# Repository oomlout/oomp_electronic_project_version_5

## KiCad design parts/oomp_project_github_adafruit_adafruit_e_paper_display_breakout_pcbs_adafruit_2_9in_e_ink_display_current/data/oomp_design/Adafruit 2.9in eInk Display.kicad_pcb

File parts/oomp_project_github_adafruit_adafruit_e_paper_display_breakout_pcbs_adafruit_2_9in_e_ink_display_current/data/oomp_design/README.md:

# OOMP KiCad design copy

Open `Adafruit 2.9in eInk Display.kicad_pro` (or the `.kicad_pcb` / `.kicad_sch`) in KiCad. Local OOMP libraries are under `libraries/`. Original inputs are preserved in [../original/](../original/).

Only verified unchanged installed KiCad defaults were renamed. Modified, custom, unmatched and unavailable items remain unchanged. Soldering variants are never swapped during conversion. Existing pad coordinates, nets and UUIDs are preserved.

See [conversion_report.yaml](conversion_report.yaml) for every conversion and skip. Copy this directory before editing; regeneration refuses to overwrite edited design files.

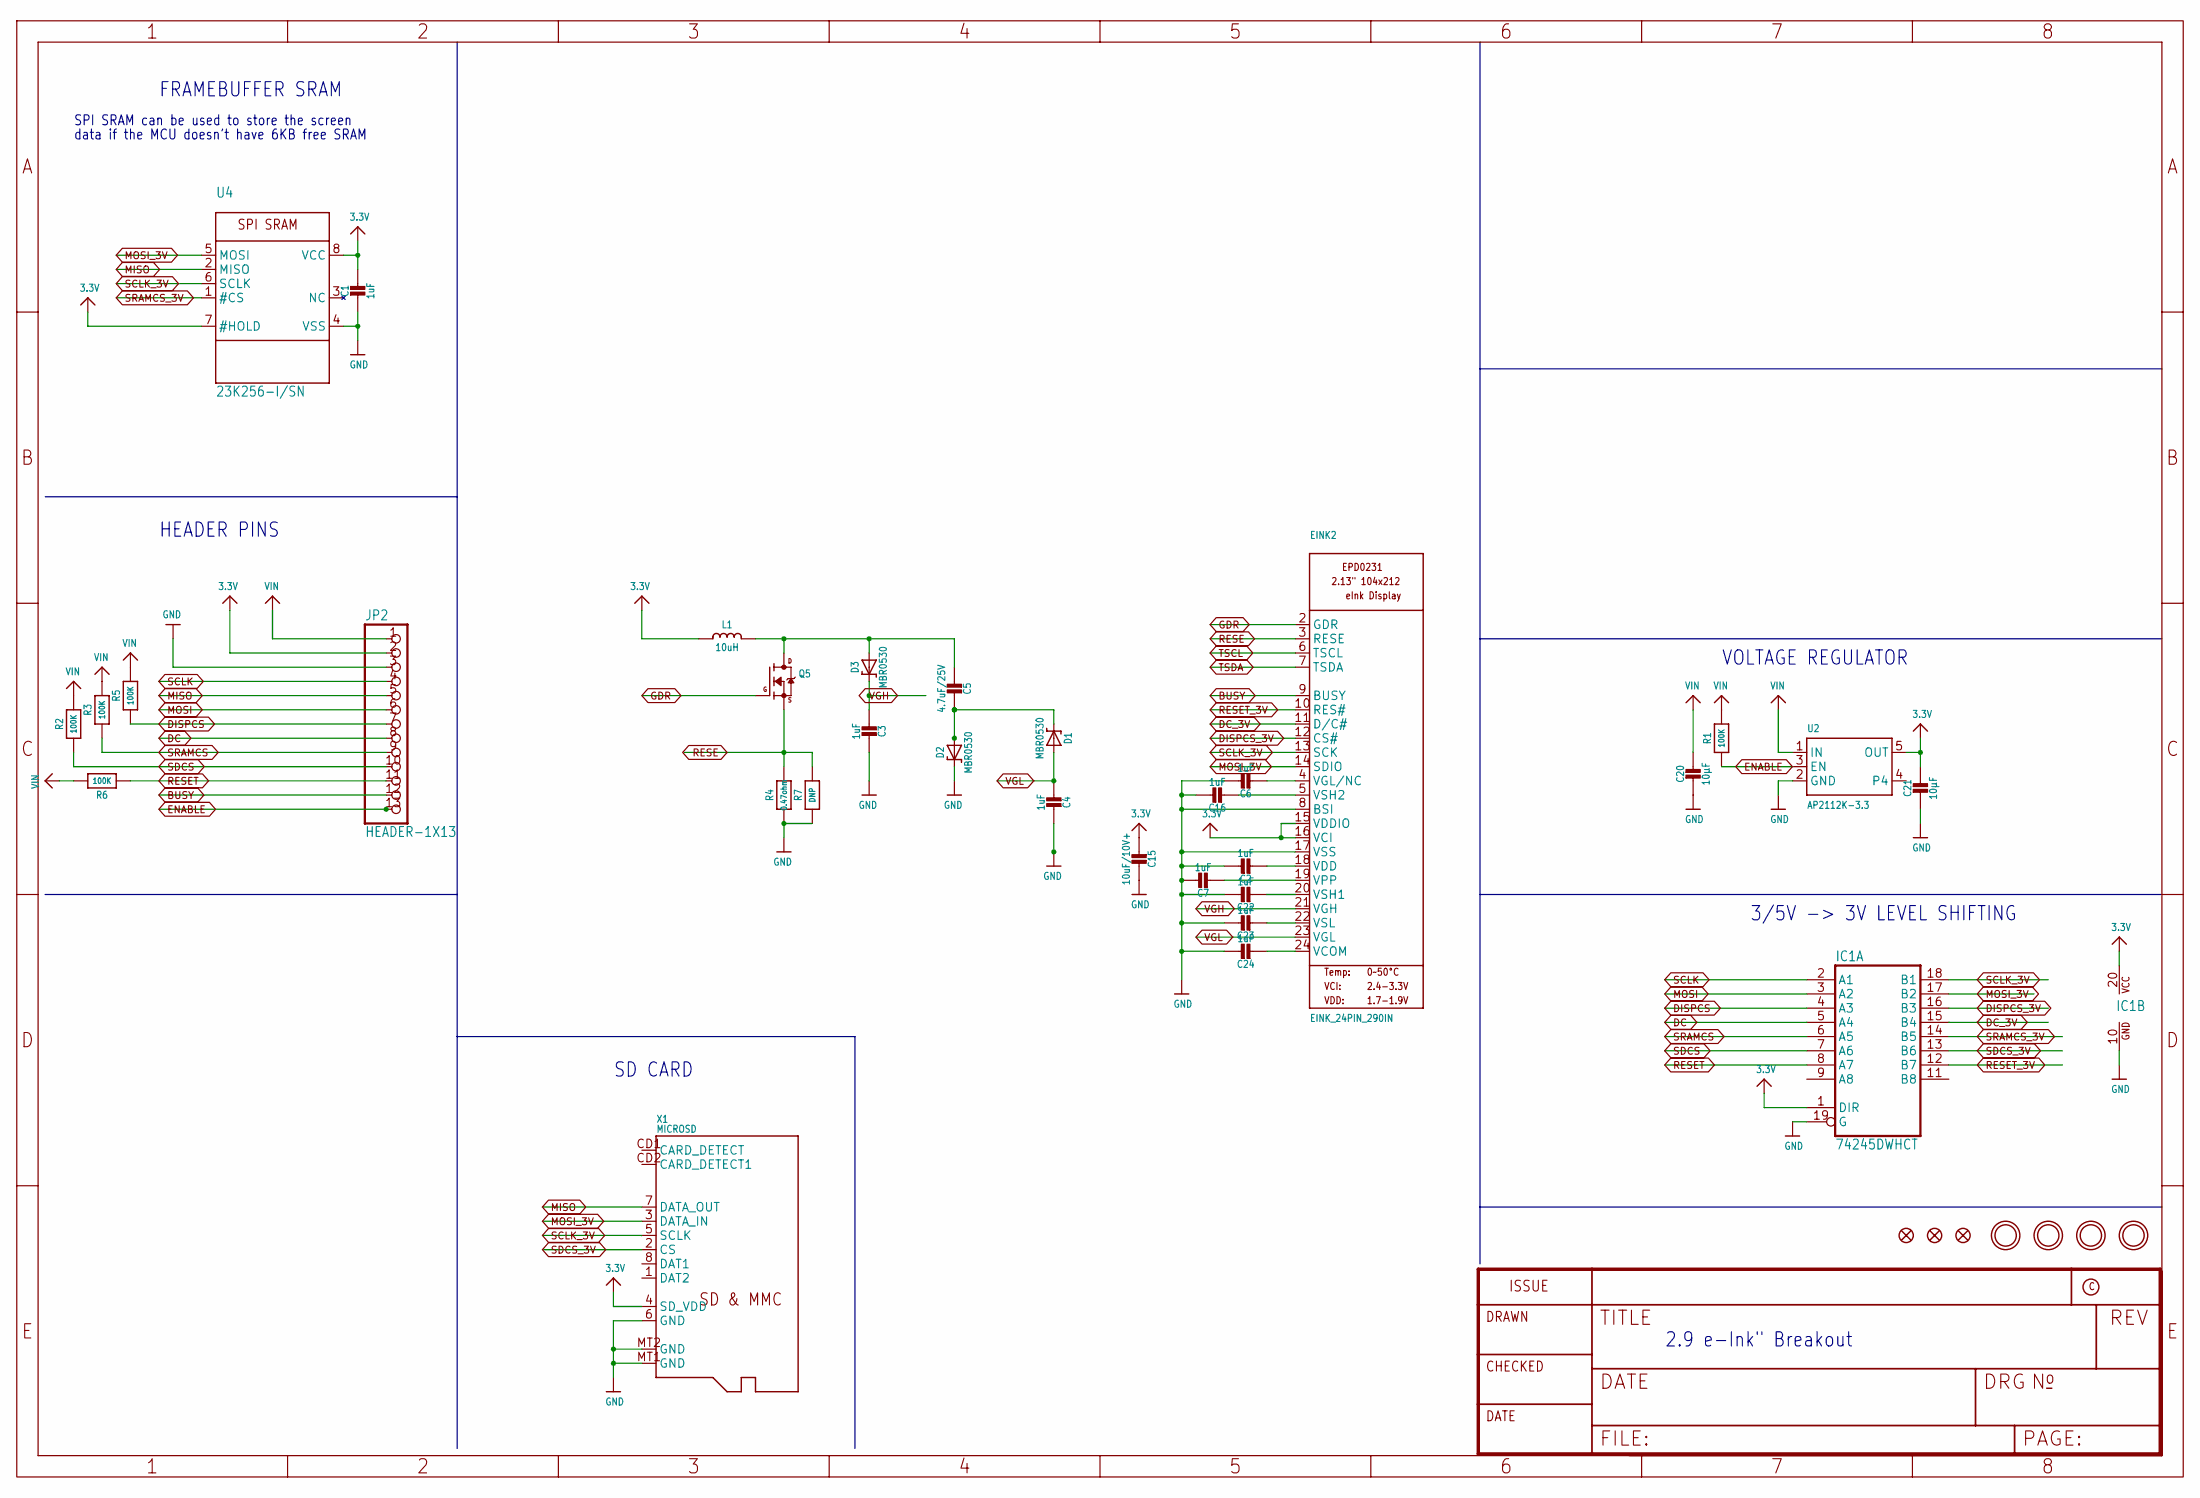
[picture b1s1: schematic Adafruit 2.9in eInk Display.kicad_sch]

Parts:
C1: 1uF; 0805_10MGAP
C2, C3, C4, C6, C7, C16, C22, C23, C24: 1uF; 0805-NO
C5: 4.7uF/25V; 0805-NO
C15: 10uF/10V+; 0805-NO
C20, C21: 10µF; 0805-NO
D1, D2, D3: MBR0530; SOD-123
EINK2: EINK_24PIN_290IN; EINK_290IN
FID1, FID2, FID3: FIDUCIAL_1MM
IC1: 74245DWHCT; SO20W
JP2: HEADER-1X13; 1X13_ROUND_70
L1: 10uH; INDUCTOR_4X4MM_NR401
Q5: IRLML0100; SOT23-3
R1, R2, R3, R5, R6: 100K; 0805-NO
R4: 0.47ohm; 0805_10MGAP
R7: DNP; 0805_10MGAP
U2: AP2112K-3.3; SOT23-5
U4: 23K256-I/SN; SOIC8_150MIL
U$3, U$4, U$5, U$6: MOUNTINGHOLE2.5; MOUNTINGHOLE_2.5_PLATED
X1: MICROSD

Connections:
3.3V: C1.1, C15.2, C21.1, EINK2.15 (VDDIO), EINK2.16 (VCI), IC1.1 (DIR), IC1.20 (VCC), JP2.2, L1.P$2 (2), U2.5 (OUT), U4.7 (#HOLD), U4.8 (VCC), X1.4 (SD_VDD)
BUSY: EINK2.9 (BUSY), JP2.12
DC: IC1.5 (A4), JP2.8
DC_3V: EINK2.11 (D/C#), IC1.15 (B4)
DISPCS: IC1.4 (A3), JP2.7, R5.1
DISPCS_3V: EINK2.12 (CS#), IC1.16 (B3)
ENABLE: JP2.13, R1.1, U2.3 (EN)
GDR: EINK2.2 (GDR), Q5.1 (G)
GND: C1.2, C2.1, C3.2, C4.2, C6.1, C7.1, C15.1, C16.1, C20.2, C21.2, C22.1, C23.1, C24.1, D2.C, EINK2.8 (BSI), EINK2.17 (VSS), IC1.10 (GND), IC1.19 (G), JP2.3, R4.2, R7.2, U2.2 (GND), U4.4 (VSS), X1.6 (GND), X1.MT1 (GND), X1.MT2 (GND)
MISO: JP2.5, U4.2 (MISO), X1.7 (DATA_OUT)
MOSI: IC1.3 (A2), JP2.6
MOSI_3V: EINK2.14 (SDIO), IC1.17 (B2), U4.5 (MOSI), X1.3 (DATA_IN)
unnamed: C7.2, EINK2.19 (VPP)
unnamed: C5.2, D1.C, D2.A
unnamed: C5.1, D3.A, L1.P$1 (1), Q5.3 (D)
unnamed: C16.2, EINK2.5 (VSH2)
unnamed: C2.2, EINK2.18 (VDD)
unnamed: C22.2, EINK2.20 (VSH1)
unnamed: C6.2, EINK2.4 (VGL/NC)
unnamed: C23.2, EINK2.22 (VSL)
unnamed: C24.2, EINK2.24 (VCOM)
RESE: EINK2.3 (RESE), Q5.2 (S), R4.1, R7.1
RESET: IC1.8 (A7), JP2.11, R6.1
RESET_3V: EINK2.10 (RES#), IC1.12 (B7)
SCLK: IC1.2 (A1), JP2.4
SCLK_3V: EINK2.13 (SCK), IC1.18 (B1), U4.6 (SCLK), X1.5 (SCLK)
SDCS: IC1.7 (A6), JP2.10, R2.1
SDCS_3V: IC1.13 (B6), X1.2 (CS)
SRAMCS: IC1.6 (A5), JP2.9, R3.1
SRAMCS_3V: IC1.14 (B5), U4.1 (#CS)
TSCL: EINK2.6 (TSCL)
TSDA: EINK2.7 (TSDA)
VGH: C3.1, D3.C, EINK2.21 (VGH)
VGL: C4.1, D1.A, EINK2.23 (VGL)
VIN: C20.1, JP2.1, R1.2, R2.2, R3.2, R5.2, R6.2, U2.1 (IN)

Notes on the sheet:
3/5V -> 3V LEVEL SHIFTING
VOLTAGE REGULATOR
2.9 e-Ink" Breakout
FRAMEBUFFER SRAM
SPI SRAM can be used to store the screen
SD CARD
HEADER PINS
data if the MCU doesn't have 6KB free SRAM

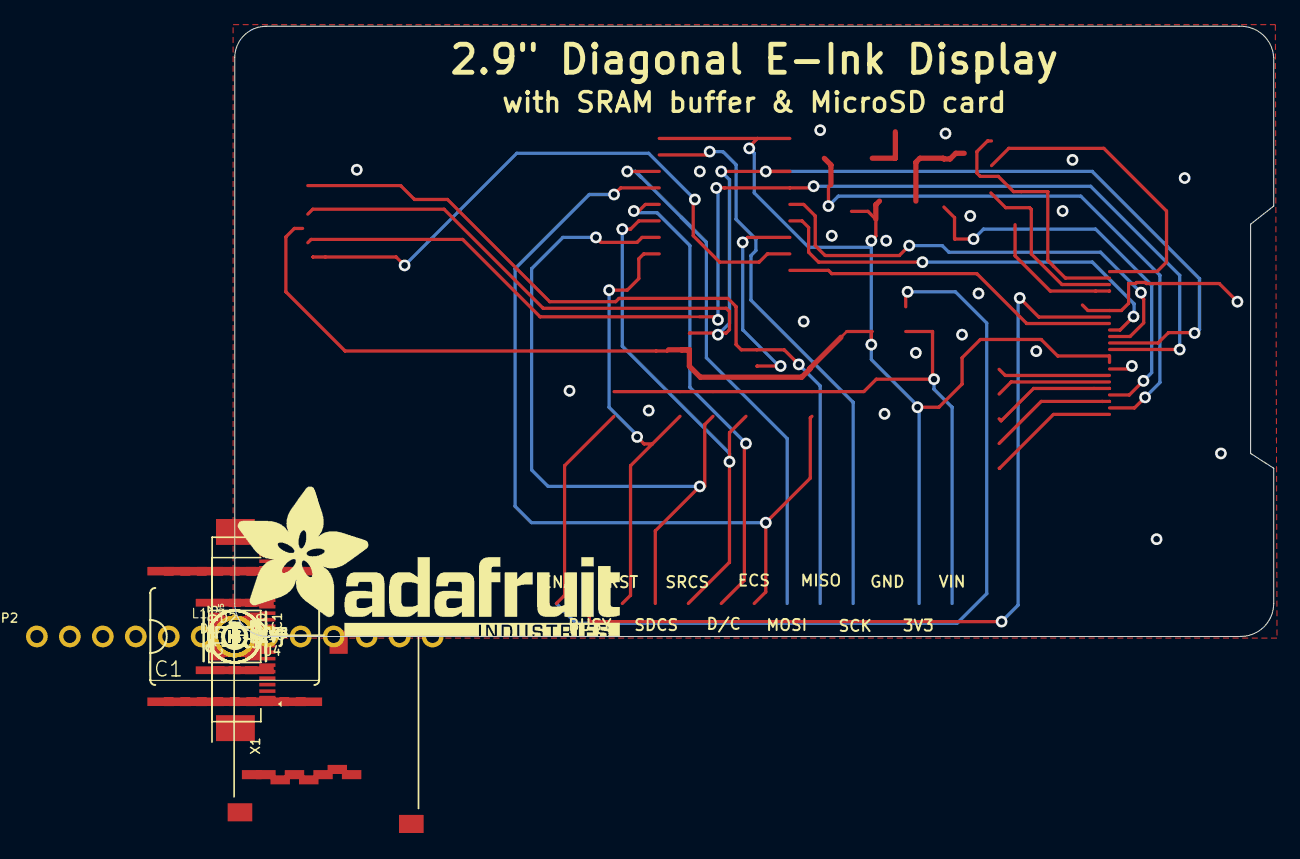
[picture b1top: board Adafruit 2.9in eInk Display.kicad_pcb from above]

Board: 2 copper layers, 80.0 x 47.0 mm, 41 parts (1 on the bottom side), 33 nets.

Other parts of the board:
U$9: PCBFEAT-REV-040
U$39: ADAFRUIT_TEXT_30MM

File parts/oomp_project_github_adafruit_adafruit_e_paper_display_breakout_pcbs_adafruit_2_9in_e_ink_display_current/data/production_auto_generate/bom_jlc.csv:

Comment,Designator,Footprint,LCSC Part #
,JP2,Adafruit 2.9in eInk Display-import-fps:1X13_ROUND_70,C2894936
,U$39,Adafruit 2.9in eInk Display-import-fps:ADAFRUIT_TEXT_30MM,
,U$9,Adafruit 2.9in eInk Display-import-fps:PCBFEAT-REV-040,
0.47ohm,R4,Adafruit 2.9in eInk Display-import-fps:0805_10MGAP,
100K,"R1,R2,R3,R5,R6",Adafruit 2.9in eInk Display-import-fps:0805-NO,C149504
10uF/10V+,C15,Adafruit 2.9in eInk Display-import-fps:0805-NO,
10uH,L1,Adafruit 2.9in eInk Display-import-fps:INDUCTOR_4X4MM_NR401,
10µF,"C20,C21",Adafruit 2.9in eInk Display-import-fps:0805-NO,
1uF,"C2,C3,C4,C6,C7,C16,C22,C23,C24",Adafruit 2.9in eInk Display-import-fps:0805-NO,
1uF,C1,Adafruit 2.9in eInk Display-import-fps:0805_10MGAP,
23K256-I/SN,U4,Adafruit 2.9in eInk Display-import-fps:SOIC8_150MIL,
4.7uF/25V,C5,Adafruit 2.9in eInk Display-import-fps:0805-NO,
74HCT245DW,IC1,Adafruit 2.9in eInk Display-import-fps:SO20W,
AP2112K-3.3,U2,Adafruit 2.9in eInk Display-import-fps:SOT23-5,
DNP,R7,Adafruit 2.9in eInk Display-import-fps:0805_10MGAP,
EINK_24PIN_290IN,EINK2,Adafruit 2.9in eInk Display-import-fps:EINK_290IN,
IRLML0100,Q5,Adafruit 2.9in eInk Display-import-fps:SOT23-3,
MBR0530,"D1,D2,D3",Adafruit 2.9in eInk Display-import-fps:SOD-123,
MICROSD,X1,Adafruit 2.9in eInk Display-import-fps:MICROSD,

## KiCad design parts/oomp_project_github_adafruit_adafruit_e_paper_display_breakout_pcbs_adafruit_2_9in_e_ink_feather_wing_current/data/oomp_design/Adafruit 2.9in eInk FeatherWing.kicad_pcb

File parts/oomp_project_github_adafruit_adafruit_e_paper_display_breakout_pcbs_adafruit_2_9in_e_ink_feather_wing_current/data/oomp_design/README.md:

# OOMP KiCad design copy

Open `Adafruit 2.9in eInk FeatherWing.kicad_pro` (or the `.kicad_pcb` / `.kicad_sch`) in KiCad. Local OOMP libraries are under `libraries/`. Original inputs are preserved in [../original/](../original/).

Only verified unchanged installed KiCad defaults were renamed. Modified, custom, unmatched and unavailable items remain unchanged. Soldering variants are never swapped during conversion. Existing pad coordinates, nets and UUIDs are preserved.

See [conversion_report.yaml](conversion_report.yaml) for every conversion and skip. Copy this directory before editing; regeneration refuses to overwrite edited design files.

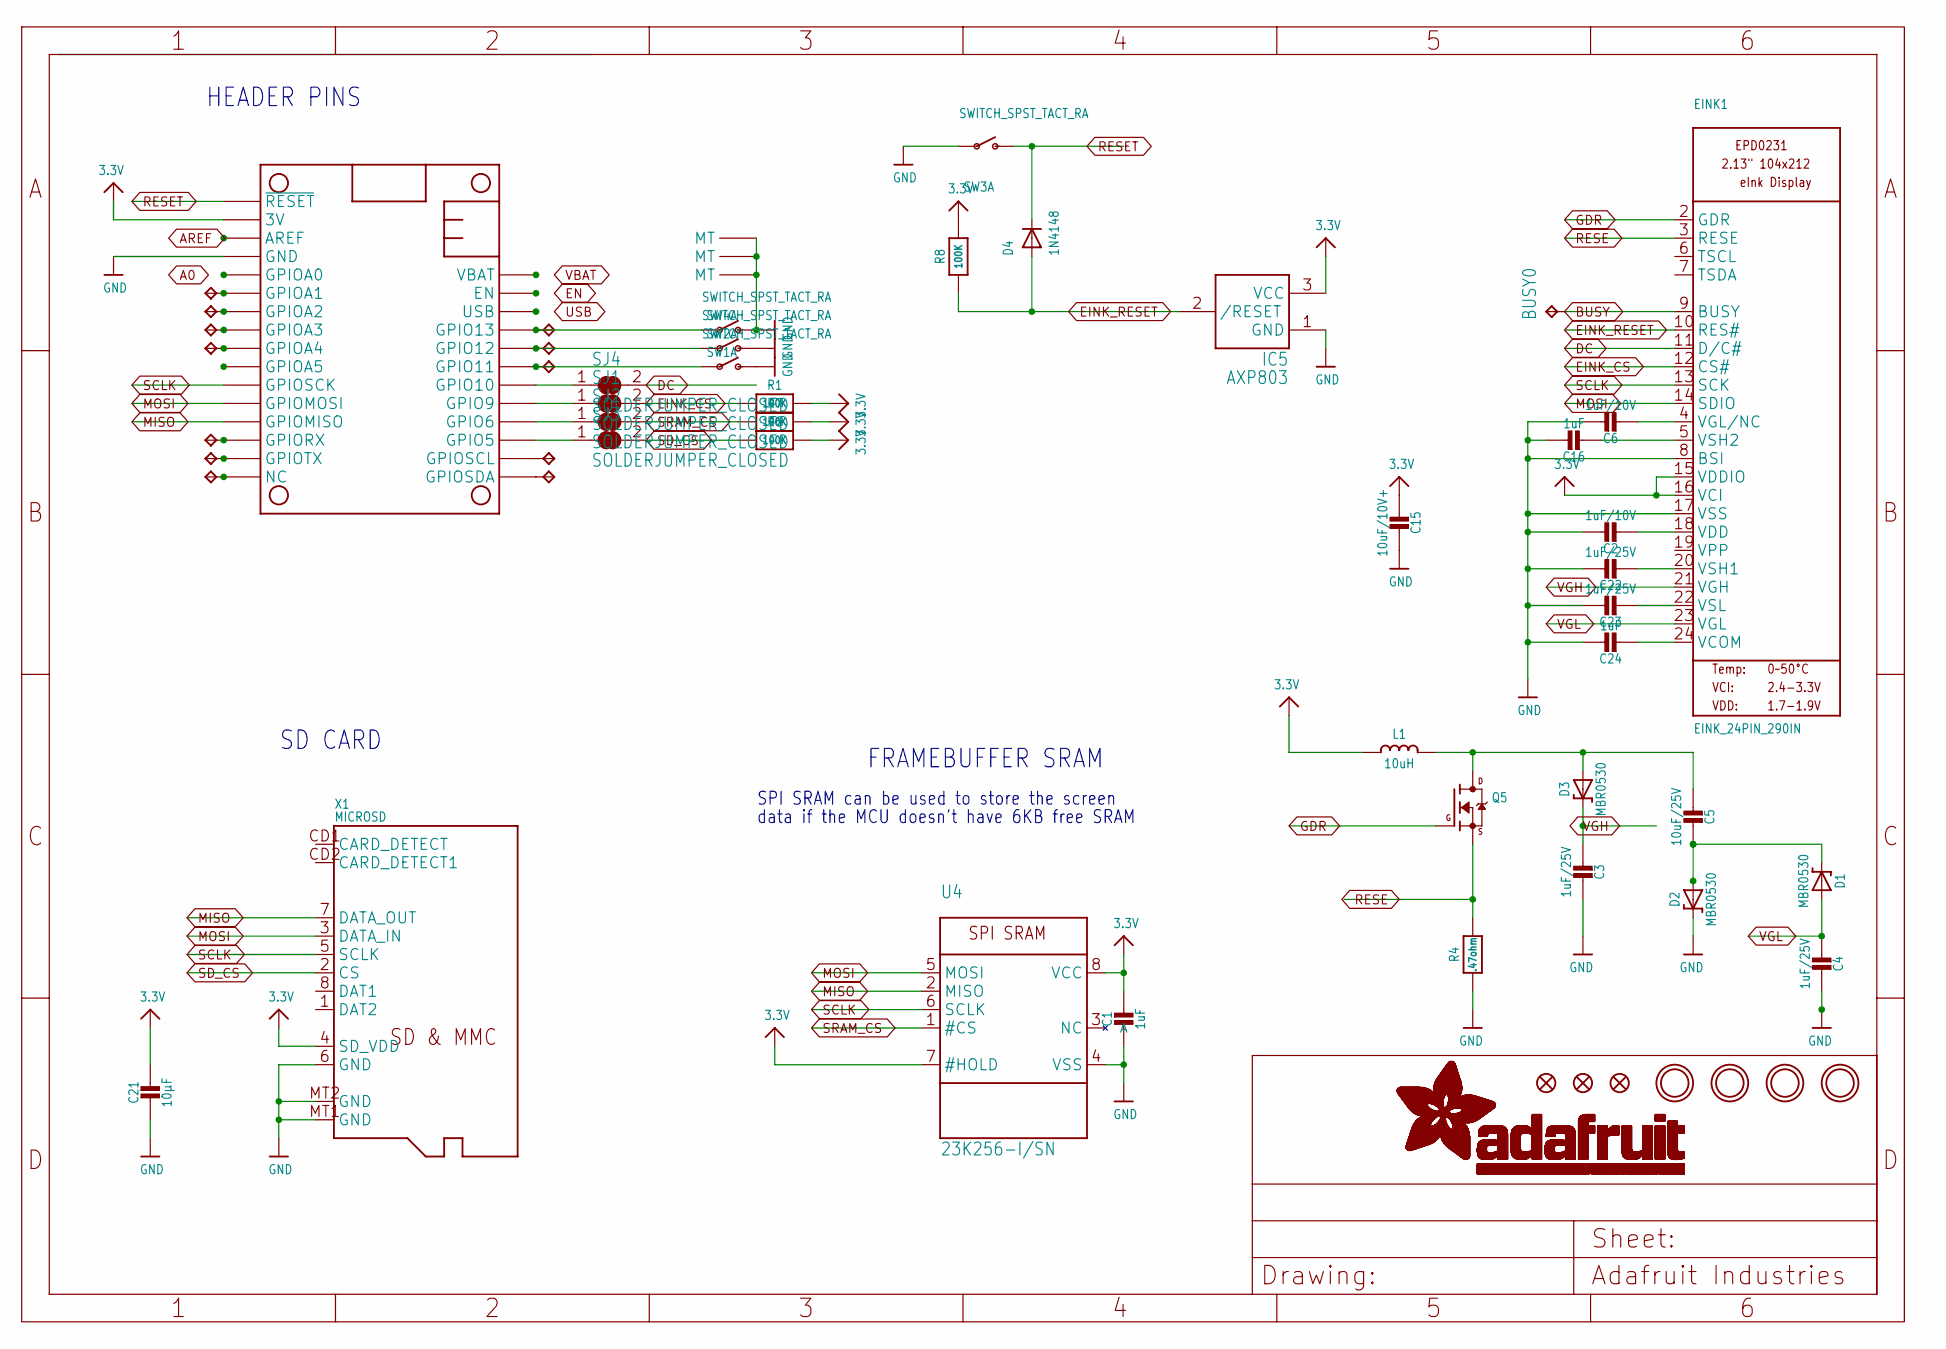
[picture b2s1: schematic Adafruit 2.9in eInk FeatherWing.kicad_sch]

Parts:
BUSY0: TPTP15SQ; TP15SQ
C1: 1uF; 0805_10MGAP
C2, C6: 1uF/10V; 0805-NO
C3, C4, C22, C23: 1uF/25V; 0805-NO
C5: 10uF/25V; 0805-NO
C15: 10uF/10V+; 0805-NO
C16, C24: 1uF; 0805-NO
C21: 10µF; 0805-NO
D1, D2, D3: MBR0530; SOD-123
D4: 1N4148; SOD-323F
EINK1: EINK_24PIN_290IN; EINK_290IN
FID1, FID2, FID3: FIDUCIAL_1MM
IC5: AXP803; SOT23
L1: 10uH; INDUCTOR_4X4MM_NR401
MS1: FEATHERWING_SMTDUALNOHOLES; FEATHERWING_SMT_NOHOLES
Q5: IRLML0100; SOT23-3
R1, R6, R7, R8: 100K; 0603-NO
R4: .47ohm; 0805_10MGAP
SJ1, SJ2, SJ3, SJ4: SOLDERJUMPER_CLOSED; SOLDERJUMPER_CLOSEDWIRE
SW1, SW2, SW3, SW4: SWITCH_SPST_TACT_RA; SPST_TACTILE_RA
TP1, TP2, TP3, TP4, TP5, TP6, TP7, TP8, TP9, TP11, TP12, TP13: TPTP15SQ; TP15SQ
U4: 23K256-I/SN; SOIC8_150MIL
U$3, U$4, U$5, U$6: MOUNTINGHOLE2.5; MOUNTINGHOLE_2.5_PLATED
X1: MICROSD

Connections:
3.3V: C1.1, C15.2, C21.1, EINK1.15 (VDDIO), EINK1.16 (VCI), IC5.3 (VCC), L1.P$2 (2), MS1.2 (3V), MS1.2B (3V), R1.2, R6.2, R7.2, R8.2, U4.7 (#HOLD), U4.8 (VCC), X1.4 (SD_VDD)
A0: MS1.5 (GPIOA0), MS1.5B (GPIOA0)
AREF: MS1.3 (AREF), MS1.3B (AREF)
BUSY: BUSY0.TP, EINK1.9 (BUSY)
DC: EINK1.11 (D/C#), SJ4.2
EINK_CS: EINK1.12 (CS#), R1.1, SJ1.2
EINK_RESET: D4.A, EINK1.10 (RES#), IC5.2 (/RESET), R8.1
EN: MS1.27 (EN), MS1.27B (EN)
GDR: EINK1.2 (GDR), Q5.1 (G)
GND: C1.2, C2.1, C3.2, C4.2, C6.1, C15.1, C16.1, C21.2, C22.1, C23.1, C24.1, D2.C, EINK1.8 (BSI), EINK1.17 (VSS), IC5.1 (GND), MS1.4 (GND), MS1.4B (GND), R4.2, SW1.2 (S), SW1.MT1 (MT), SW1.MT2 (MT), SW2.2 (S), SW2.MT1 (MT), SW2.MT2 (MT), SW3.1, SW4.2 (S), SW4.MT1 (MT), SW4.MT2 (MT), U4.4 (VSS), X1.6 (GND), X1.MT1 (GND), X1.MT2 (GND)
H: MS1.19 (GPIO5), MS1.19B (GPIO5), SJ3.1
I: MS1.20 (GPIO6), MS1.20B (GPIO6), SJ2.1
J: MS1.21 (GPIO9), MS1.21B (GPIO9), SJ1.1
K: MS1.22 (GPIO10), MS1.22B (GPIO10), SJ4.1
MISO: MS1.13 (GPIOMISO), MS1.13B (GPIOMISO), U4.2 (MISO), X1.7 (DATA_OUT)
MOSI: EINK1.14 (SDIO), MS1.12 (GPIOMOSI), MS1.12B (GPIOMOSI), U4.5 (MOSI), X1.3 (DATA_IN)
unnamed: MS1.10 (GPIOA5), MS1.10B (GPIOA5)
unnamed: C5.2, D1.C, D2.A
unnamed: C5.1, D3.A, L1.P$1 (1), Q5.3 (D)
unnamed: C16.2, EINK1.5 (VSH2)
unnamed: C2.2, EINK1.18 (VDD)
unnamed: C22.2, EINK1.20 (VSH1)
unnamed: MS1.6 (GPIOA1), MS1.6B (GPIOA1), TP6.TP
unnamed: C6.2, EINK1.4 (VGL/NC)
unnamed: MS1.7 (GPIOA2), MS1.7B (GPIOA2), TP7.TP
unnamed: MS1.8 (GPIOA3), MS1.8B (GPIOA3), TP8.TP
unnamed: MS1.9 (GPIOA4), MS1.9B (GPIOA4), TP9.TP
unnamed: MS1.14 (GPIORX), MS1.14B (GPIORX), TP11.TP
unnamed: MS1.15 (GPIOTX), MS1.15B (GPIOTX), TP12.TP
unnamed: MS1.16 (NC), MS1.16B (NC), TP13.TP
unnamed: MS1.17 (GPIOSDA), MS1.17B (GPIOSDA), TP4.TP
unnamed: MS1.18 (GPIOSCL), MS1.18B (GPIOSCL), TP3.TP
unnamed: MS1.23 (GPIO11), MS1.23B (GPIO11), SW1.1, TP1.TP
unnamed: MS1.24 (GPIO12), MS1.24B (GPIO12), SW2.1, TP2.TP
unnamed: MS1.25 (GPIO13), MS1.25B (GPIO13), SW4.1, TP5.TP
unnamed: C23.2, EINK1.22 (VSL)
unnamed: C24.2, EINK1.24 (VCOM)
RESE: EINK1.3 (RESE), Q5.2 (S), R4.1
RESET: D4.C, MS1.1 (~RESET), MS1.1B (~RESET), SW3.2 (S)
SCLK: EINK1.13 (SCK), MS1.11 (GPIOSCK), MS1.11B (GPIOSCK), U4.6 (SCLK), X1.5 (SCLK)
SD_CS: R6.1, SJ3.2, X1.2 (CS)
SRAM_CS: R7.1, SJ2.2, U4.1 (#CS)
USB: MS1.26 (USB), MS1.26B (USB)
VBAT: MS1.28 (VBAT), MS1.28B (VBAT)
VGH: C3.1, D3.C, EINK1.21 (VGH)
VGL: C4.1, D1.A, EINK1.23 (VGL)

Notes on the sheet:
FRAMEBUFFER SRAM
data if the MCU doesn't have 6KB free SRAM
HEADER PINS
SPI SRAM can be used to store the screen
SD CARD

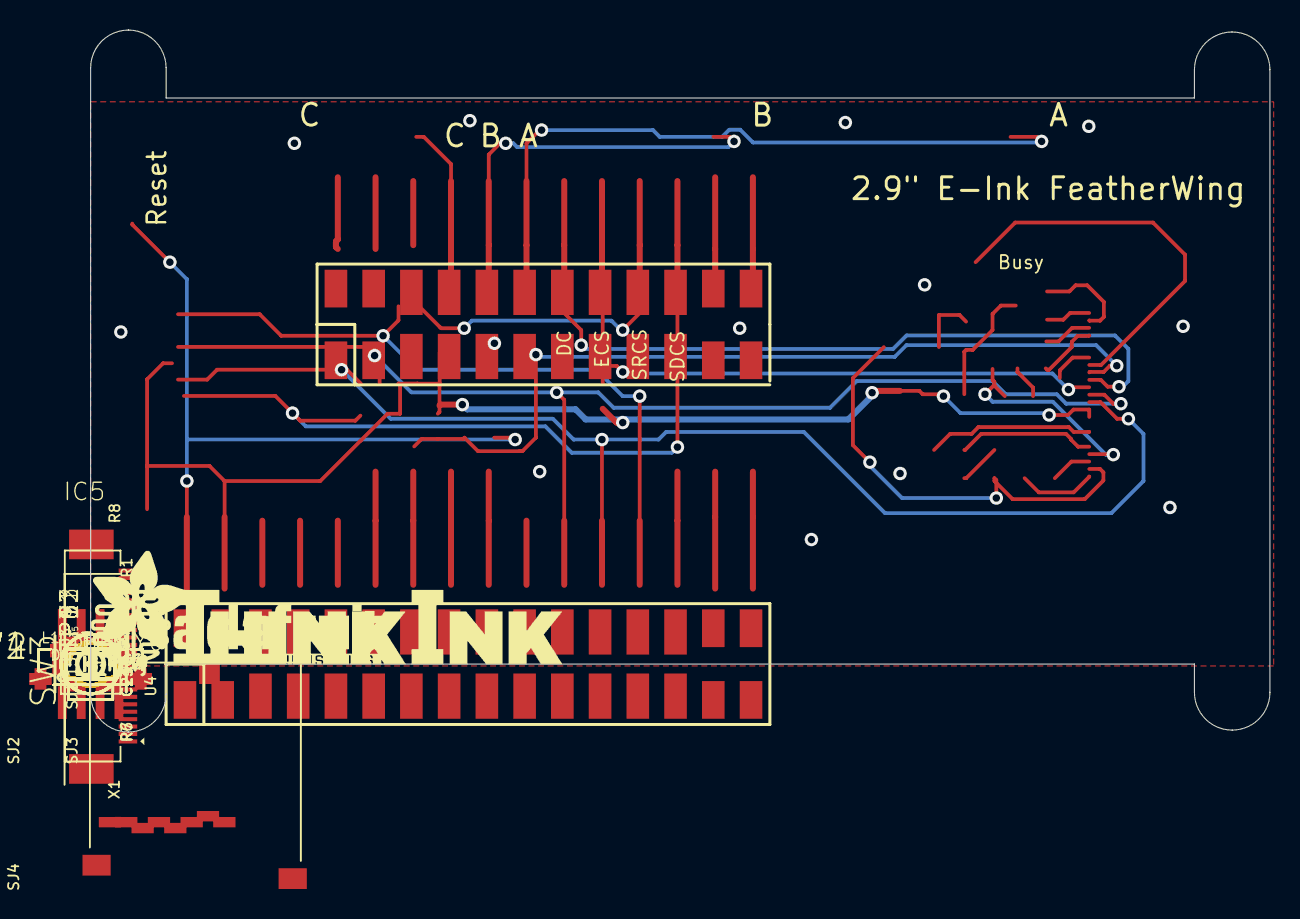
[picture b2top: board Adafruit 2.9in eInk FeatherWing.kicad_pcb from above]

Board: 2 copper layers, 79.4 x 47.2 mm, 59 parts (1 on the bottom side), 46 nets.

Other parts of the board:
U$8: THINKINK_1.25IN
U$9: PCBFEAT-REV-040
U$17: ADAFRUIT_TEXT_20MM

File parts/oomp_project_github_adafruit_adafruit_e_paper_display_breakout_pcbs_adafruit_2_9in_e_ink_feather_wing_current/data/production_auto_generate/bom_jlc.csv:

Comment,Designator,Footprint,LCSC Part #
,U$17,Adafruit 2.9in eInk FeatherWing-import-fps:ADAFRUIT_TEXT_20MM,
,U$9,Adafruit 2.9in eInk FeatherWing-import-fps:PCBFEAT-REV-040,
,"SW1,SW2,SW3,SW4",Adafruit 2.9in eInk FeatherWing-import-fps:SPST_TACTILE_RA,
,U$8,Adafruit 2.9in eInk FeatherWing-import-fps:THINKINK_1.25IN,
.47ohm,R4,Adafruit 2.9in eInk FeatherWing-import-fps:0805_10MGAP,
100K,"R1,R6,R7,R8",Adafruit 2.9in eInk FeatherWing-import-fps:0603-NO,C25803
10uF/10V+,C15,Adafruit 2.9in eInk FeatherWing-import-fps:0805-NO,
10uF/25V,C5,Adafruit 2.9in eInk FeatherWing-import-fps:0805-NO,
10uH,L1,Adafruit 2.9in eInk FeatherWing-import-fps:INDUCTOR_4X4MM_NR401,
10µF,C21,Adafruit 2.9in eInk FeatherWing-import-fps:0805-NO,
1N4148,D4,Adafruit 2.9in eInk FeatherWing-import-fps:SOD-323F,
1uF,"C16,C24",Adafruit 2.9in eInk FeatherWing-import-fps:0805-NO,
1uF,C1,Adafruit 2.9in eInk FeatherWing-import-fps:0805_10MGAP,
1uF/10V,"C2,C6",Adafruit 2.9in eInk FeatherWing-import-fps:0805-NO,
1uF/25V,"C3,C4,C22,C23",Adafruit 2.9in eInk FeatherWing-import-fps:0805-NO,
23K256-I/SN,U4,Adafruit 2.9in eInk FeatherWing-import-fps:SOIC8_150MIL,
AXP803,IC5,Adafruit 2.9in eInk FeatherWing-import-fps:SOT23,
EINK_24PIN_290IN,EINK1,Adafruit 2.9in eInk FeatherWing-import-fps:EINK_290IN,
FEATHERWING_SMTDUALNOHOLES,MS1,Adafruit 2.9in eInk FeatherWing-import-fps:FEATHERWING_SMT_NOHOLES,
IRLML0100,Q5,Adafruit 2.9in eInk FeatherWing-import-fps:SOT23-3,
MBR0530,"D1,D2,D3",Adafruit 2.9in eInk FeatherWing-import-fps:SOD-123,
MICROSD,X1,Adafruit 2.9in eInk FeatherWing-import-fps:MICROSD,
TPTP15SQ,"BUSY0,TP1,TP2,TP3,TP4,TP5,TP6,TP7,TP8,TP9,TP11,TP12,TP13",Adafruit 2.9in eInk FeatherWing-import-fps:TP15SQ,

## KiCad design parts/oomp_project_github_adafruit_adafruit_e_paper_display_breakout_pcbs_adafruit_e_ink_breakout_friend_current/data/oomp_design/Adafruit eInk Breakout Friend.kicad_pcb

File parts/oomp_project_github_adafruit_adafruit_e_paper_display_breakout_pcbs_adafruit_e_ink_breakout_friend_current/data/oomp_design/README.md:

# OOMP KiCad design copy

Open `Adafruit eInk Breakout Friend.kicad_pro` (or the `.kicad_pcb` / `.kicad_sch`) in KiCad. Local OOMP libraries are under `libraries/`. Original inputs are preserved in [../original/](../original/).

Only verified unchanged installed KiCad defaults were renamed. Modified, custom, unmatched and unavailable items remain unchanged. Soldering variants are never swapped during conversion. Existing pad coordinates, nets and UUIDs are preserved.

See [conversion_report.yaml](conversion_report.yaml) for every conversion and skip. Copy this directory before editing; regeneration refuses to overwrite edited design files.

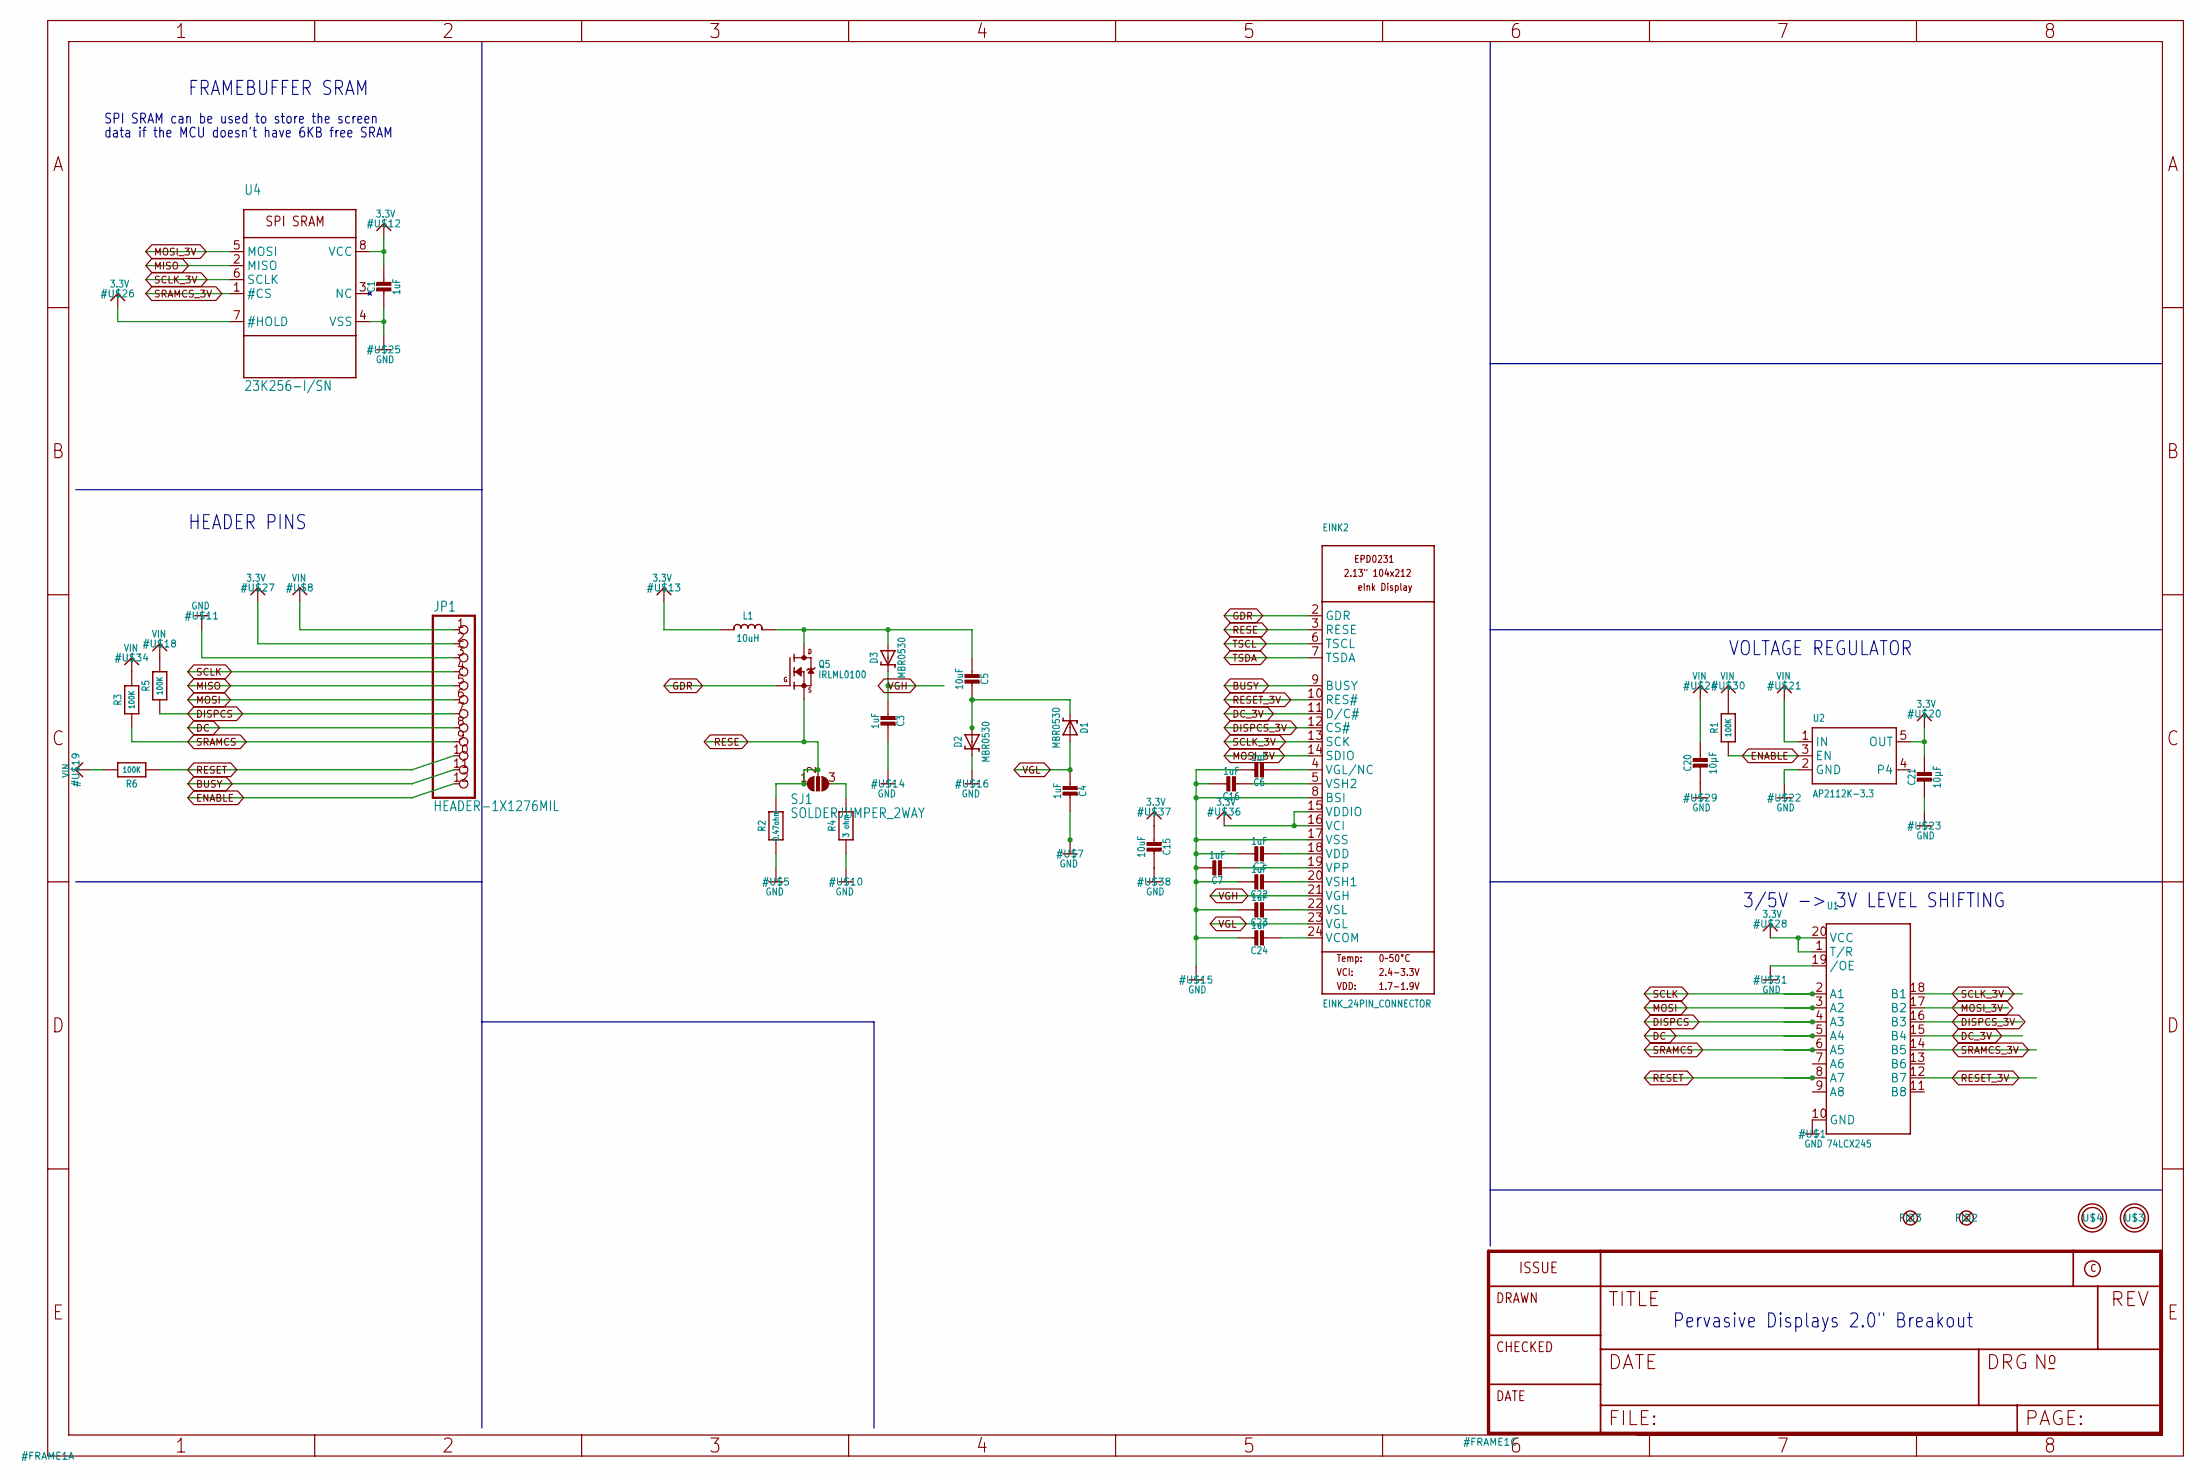
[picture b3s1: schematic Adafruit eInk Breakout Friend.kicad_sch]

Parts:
C1: 1uF; 0805_10MGAP
C2, C3, C4, C6, C7, C16, C22, C23, C24: 1uF; 0805-NO
C5, C15: 10uF; 0805-NO
C20, C21: 10µF; 0805-NO
D1, D2, D3: MBR0530; SOD-123
EINK2: EINK_24PIN_CONNECTOR; EINK_24PIN
FID2, FID3: FIDUCIAL_1MM
JP1: HEADER-1X1276MIL; 1X12_ROUND_76MIL
L1: 10uH; INDUCTOR_4X4MM_NR401
Q5: IRLML0100; SOT23-3
R1, R3, R5, R6: 100K; 0603-NO
R2: 0.47ohm; 0805-NO
R4: 3 ohm; 0805-NO
SJ1: SOLDERJUMPER_2WAY; SOLDERJUMPER_2WAY_OPEN_NOPASTE
U1: 74LCX245; TSSOP20
U2: AP2112K-3.3; SOT23-5
U4: 23K256-I/SN; SOIC8_150MIL
U$3, U$4: MOUNTINGHOLE2.5; MOUNTINGHOLE_2.5_PLATED

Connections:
3.3V: C1.1, C15.2, C21.1, EINK2.15 (VDDIO), EINK2.16 (VCI), JP1.2, L1.P$2 (2), U1.1 (T/R), U1.20 (VCC), U2.5 (OUT), U4.7 (#HOLD), U4.8 (VCC)
BUSY: EINK2.9 (BUSY), JP1.11
DC: JP1.8, U1.5 (A4)
DC_3V: EINK2.11 (D/C#), U1.15 (B4)
DISPCS: JP1.7, R5.1, U1.4 (A3)
DISPCS_3V: EINK2.12 (CS#), U1.16 (B3)
ENABLE: JP1.12, R1.1, U2.3 (EN)
GDR: EINK2.2 (GDR), Q5.1 (G)
GND: C1.2, C2.1, C3.2, C4.2, C6.1, C7.1, C15.1, C16.1, C20.2, C21.2, C22.1, C23.1, C24.1, D2.C, EINK2.8 (BSI), EINK2.17 (VSS), JP1.3, R2.2, R4.2, U1.10 (GND), U1.19 (/OE), U2.2 (GND), U4.4 (VSS)
MISO: JP1.5, U4.2 (MISO)
MOSI: JP1.6, U1.3 (A2)
MOSI_3V: EINK2.14 (SDIO), U1.17 (B2), U4.5 (MOSI)
unnamed: C7.2, EINK2.19 (VPP)
unnamed: C5.2, D1.C, D2.A
unnamed: C5.1, D3.A, L1.P$1 (1), Q5.3 (D)
unnamed: C16.2, EINK2.5 (VSH2)
unnamed: C2.2, EINK2.18 (VDD)
unnamed: C22.2, EINK2.20 (VSH1)
unnamed: R4.1, SJ1.3
unnamed: C6.2, EINK2.4 (VGL/NC)
unnamed: C23.2, EINK2.22 (VSL)
unnamed: C24.2, EINK2.24 (VCOM)
RESE: EINK2.3 (RESE), Q5.2 (S), R2.1, SJ1.1, SJ1.2
RESET: JP1.10, R6.1, U1.8 (A7)
RESET_3V: EINK2.10 (RES#), U1.12 (B7)
SCLK: JP1.4, U1.2 (A1)
SCLK_3V: EINK2.13 (SCK), U1.18 (B1), U4.6 (SCLK)
SRAMCS: JP1.9, R3.1, U1.6 (A5)
SRAMCS_3V: U1.14 (B5), U4.1 (#CS)
TSCL: EINK2.6 (TSCL)
TSDA: EINK2.7 (TSDA)
VGH: C3.1, D3.C, EINK2.21 (VGH)
VGL: C4.1, D1.A, EINK2.23 (VGL)
VIN: C20.1, JP1.1, R1.2, R3.2, R5.2, R6.2, U2.1 (IN)

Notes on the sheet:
SPI SRAM can be used to store the screen
FRAMEBUFFER SRAM
VOLTAGE REGULATOR
3/5V -> 3V LEVEL SHIFTING
Pervasive Displays 2.0" Breakout
HEADER PINS
data if the MCU doesn't have 6KB free SRAM

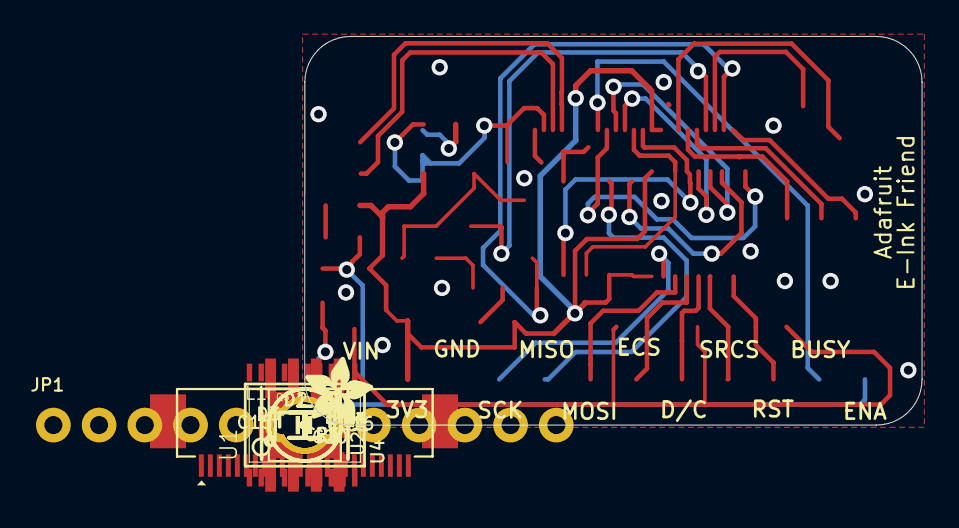
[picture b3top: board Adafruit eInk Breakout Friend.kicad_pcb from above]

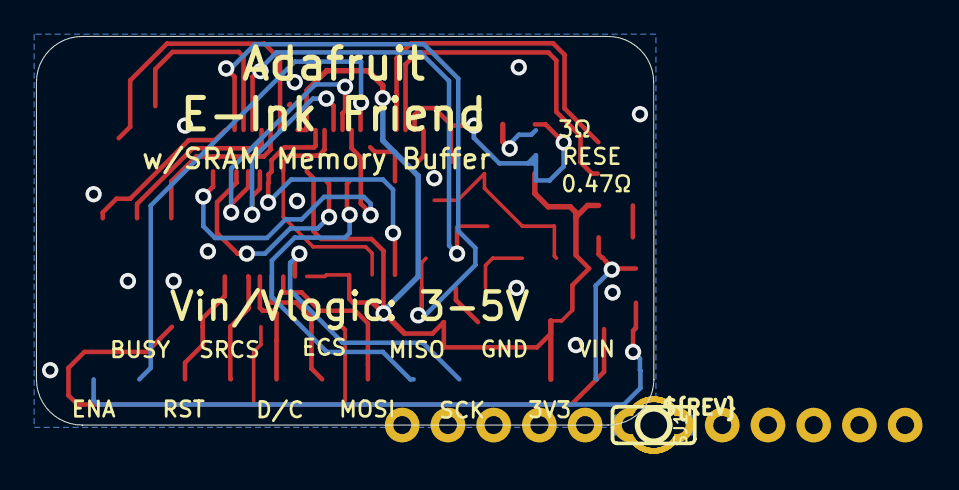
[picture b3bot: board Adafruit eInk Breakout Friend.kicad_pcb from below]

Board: 2 copper layers, 34.3 x 21.6 mm, 37 parts (2 on the bottom side), 32 nets.

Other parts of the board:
U$2: ADAFRUIT_3.5MM
U$9: PCBFEAT-REV-040

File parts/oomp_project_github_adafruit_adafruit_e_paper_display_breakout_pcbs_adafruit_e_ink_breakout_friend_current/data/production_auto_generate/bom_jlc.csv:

Comment,Designator,Footprint,LCSC Part #
,JP1,Adafruit eInk Breakout Friend-import-fps:1X12_ROUND_76MIL,C7501588
,U$2,Adafruit eInk Breakout Friend-import-fps:ADAFRUIT_3.5MM,
,U$9,Adafruit eInk Breakout Friend-import-fps:PCBFEAT-REV-040,
,U1,Adafruit eInk Breakout Friend-import-fps:TSSOP20,
0.47ohm,R2,Adafruit eInk Breakout Friend-import-fps:0805-NO,
100K,"R1,R3,R5,R6",Adafruit eInk Breakout Friend-import-fps:0603-NO,C25803
10uF,"C5,C15",Adafruit eInk Breakout Friend-import-fps:0805-NO,
10uH,L1,Adafruit eInk Breakout Friend-import-fps:INDUCTOR_4X4MM_NR401,
10µF,"C20,C21",Adafruit eInk Breakout Friend-import-fps:0805-NO,
1uF,"C2,C3,C4,C6,C7,C16,C22,C23,C24",Adafruit eInk Breakout Friend-import-fps:0805-NO,
1uF,C1,Adafruit eInk Breakout Friend-import-fps:0805_10MGAP,
23K256-I/SN,U4,Adafruit eInk Breakout Friend-import-fps:SOIC8_150MIL,
3 ohm,R4,Adafruit eInk Breakout Friend-import-fps:0805-NO,
AP2112K-3.3,U2,Adafruit eInk Breakout Friend-import-fps:SOT23-5,
EINK_24PIN_CONNECTOR,EINK2,Adafruit eInk Breakout Friend-import-fps:EINK_24PIN,
IRLML0100,Q5,Adafruit eInk Breakout Friend-import-fps:SOT23-3,
MBR0530,"D1,D2,D3",Adafruit eInk Breakout Friend-import-fps:SOD-123,
